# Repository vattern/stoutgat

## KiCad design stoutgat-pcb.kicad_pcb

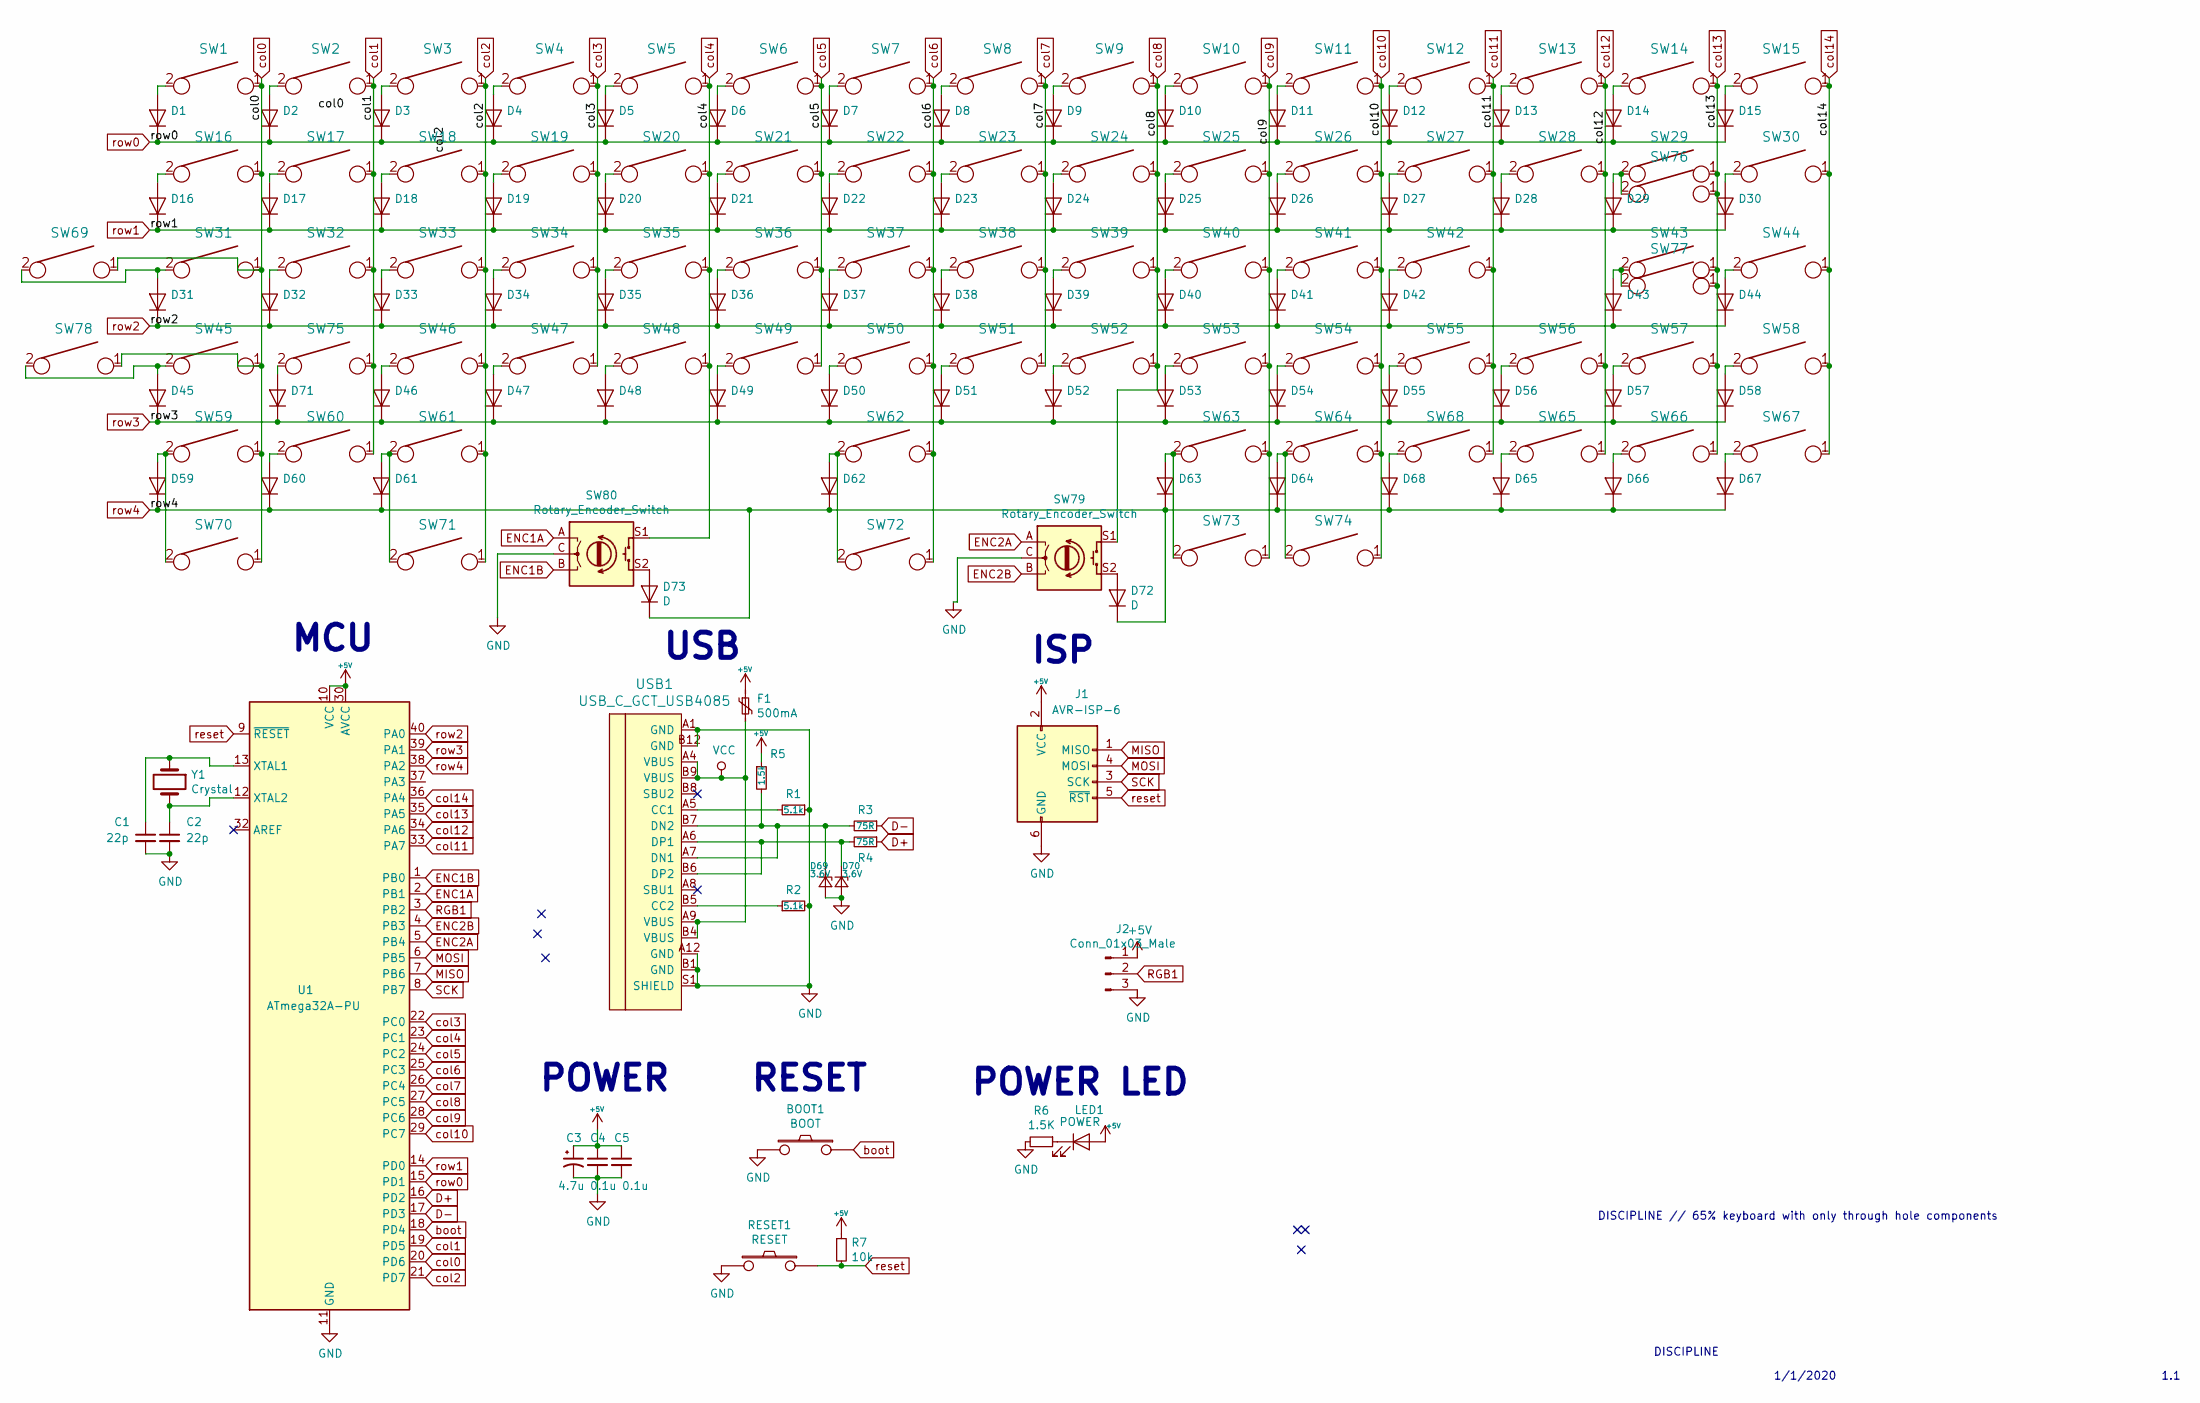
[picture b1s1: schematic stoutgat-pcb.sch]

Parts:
BOOT1: BOOT; SW_PUSH_6mm
C1, C2: 22p; C_Disc_D3.0mm_W1.6mm_P2.50mm
C3: 4.7u; CP_Radial_D4.0mm_P1.50mm
C4, C5: 0.1u; C_Disc_D4.3mm_W1.9mm_P5.00mm
D1, D2, D3, D4, D5, D6, D7, D8, D9, D10, D11, D12, D13, D14, D15, D16, D17, D18, D19, D20, D21, D22, D23, D24, D25, D26, D27, D28, D29, D30, D31, D32, D33, D34, D35, D36, D37, D38, D39, D40, D41, D42, D43, D44, D45, D46, D47, D48, D49, D50, D51, D52, D53, D54, D55, D56, D57, D58, D59, D60, D61, D62, D63, D64, D65, D66, D67, D68, D71: D_DO-35_SOD27_P7.62mm_Horizontal
D69, D70: 3.6V; D_DO-35_SOD27_P7.62mm_Horizontal
D72, D73: D; D_A-405_P7.62mm_Horizontal
F1: 500mA; C_Disc_D5.0mm_W2.5mm_P5.00mm
J1: AVR-ISP-6; PinHeader_2x03_P2.54mm_Vertical
J2: Conn_01x03_Male; PinHeader_1x03_P2.54mm_Vertical
LED1: POWER; LED_D3.0mm
R1, R2: 5.1k; R_Axial_DIN0204_L3.6mm_D1.6mm_P5.08mm_Horizontal
R3, R4: 75R; R_Axial_DIN0204_L3.6mm_D1.6mm_P5.08mm_Horizontal
R5: 1.5k; R_Axial_DIN0204_L3.6mm_D1.6mm_P5.08mm_Horizontal
R6: 1.5K; R_Axial_DIN0204_L3.6mm_D1.6mm_P5.08mm_Horizontal
R7: 10k; R_Axial_DIN0204_L3.6mm_D1.6mm_P5.08mm_Horizontal
RESET1: RESET; SW_PUSH_6mm
SW1, SW2, SW3, SW4, SW5, SW6, SW7, SW8, SW9, SW10, SW11, SW12, SW13, SW15, SW17, SW18, SW19, SW20, SW21, SW22, SW23, SW24, SW25, SW26, SW27, SW28, SW30, SW32, SW33, SW34, SW35, SW36, SW37, SW38, SW39, SW40, SW41, SW42, SW44, SW46, SW47, SW48, SW49, SW50, SW51, SW52, SW53, SW54, SW55, SW57, SW58, SW62, SW65, SW66, SW67, SW68, SW72, SW75, SW77: KEYSW; SW_Cherry_MX_1.00u_PCB
SW14: KEYSW; SW_Cherry_MX_2.00u_PCB
SW16, SW29, SW70, SW71, SW73, SW74: KEYSW; SW_Cherry_MX_1.50u_PCB
SW31, SW56: KEYSW; SW_Cherry_MX_1.75u_PCB
SW43, SW45: KEYSW; SW_Cherry_MX_2.25u_PCB
SW59, SW60, SW61, SW63, SW64, SW69, SW78: KEYSW; SW_Cherry_MX_1.25u_PCB
SW76: KEYSW; SW_Cherry_MX_ISOEnter_PCB
SW79, SW80: Rotary_Encoder_Switch; RotaryEncoder_Alps_EC11E-Switch_Vertical_H20mm
U1: ATmega32A-PU; DIP-40_W15.24mm_Socket
USB1: USB_C_GCT_USB4085; USB_C_Receptacle_GCT_USB4085
Y1: Crystal; Crystal_HC49-4H_Vertical

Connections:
+5V: C3.1, C4.1, C5.1, F1.1, J1.2 (VCC), J2.1, LED1.2 (A), R5.1, R7.1, U1.10 (VCC), U1.30 (AVCC)
D+: R4.1, U1.16 (PD2)
D-: R3.1, U1.17 (PD3)
ENC1A: SW80.A, U1.2 (PB1)
ENC1B: SW80.B, U1.1 (PB0)
ENC2A: SW79.A, U1.5 (PB4)
ENC2B: SW79.B, U1.4 (PB3)
GND: BOOT1.1, C1.2, C2.2, C3.2, C4.2, C5.2, D69.2 (A), D70.2 (A), J1.6 (GND), J2.3, R1.1, R2.2, R6.2, RESET1.1, SW79.C, SW80.C, U1.11 (GND), U1.31 (GND), USB1.A1 (GND), USB1.A12 (GND), USB1.B1 (GND), USB1.B12 (GND), USB1.S1 (SHIELD)
MISO: J1.1 (MISO), U1.7 (PB6)
MOSI: J1.4 (MOSI), U1.6 (PB5)
unnamed: C1.1, U1.13 (XTAL1), Y1.1
unnamed: C2.1, U1.12 (XTAL2), Y1.2
unnamed: D1.2 (A), SW1.2
unnamed: D2.2 (A), SW2.2
unnamed: D3.2 (A), SW3.2
unnamed: D4.2 (A), SW4.2
unnamed: D5.2 (A), SW5.2
unnamed: D6.2 (A), SW6.2
unnamed: D7.2 (A), SW7.2
unnamed: D8.2 (A), SW8.2
unnamed: D9.2 (A), SW9.2
unnamed: D10.2 (A), SW10.2
unnamed: D11.2 (A), SW11.2
unnamed: D12.2 (A), SW12.2
unnamed: D13.2 (A), SW13.2
unnamed: D14.2 (A), SW14.2
unnamed: D15.2 (A), SW15.2
unnamed: D16.2 (A), SW16.2
unnamed: D17.2 (A), SW17.2
unnamed: D18.2 (A), SW18.2
unnamed: D19.2 (A), SW19.2
unnamed: D20.2 (A), SW20.2
unnamed: D21.2 (A), SW21.2
unnamed: D22.2 (A), SW22.2
unnamed: D23.2 (A), SW23.2
unnamed: D24.2 (A), SW24.2
unnamed: D25.2 (A), SW25.2
unnamed: D26.2 (A), SW26.2
unnamed: D27.2 (A), SW27.2
unnamed: D28.2 (A), SW28.2
unnamed: D29.2 (A), SW29.2, SW76.2
unnamed: D30.2 (A), SW30.2
unnamed: D31.2 (A), SW31.2, SW69.2
unnamed: D32.2 (A), SW32.2
unnamed: D33.2 (A), SW33.2
unnamed: D34.2 (A), SW34.2
unnamed: D35.2 (A), SW35.2
unnamed: D36.2 (A), SW36.2
unnamed: D37.2 (A), SW37.2
unnamed: D38.2 (A), SW38.2
unnamed: D39.2 (A), SW39.2
unnamed: D40.2 (A), SW40.2
unnamed: D41.2 (A), SW41.2
unnamed: D42.2 (A), SW42.2
unnamed: D43.2 (A), SW43.2, SW77.2
unnamed: D44.2 (A), SW44.2
unnamed: D45.2 (A), SW45.2, SW78.2
unnamed: D46.2 (A), SW46.2
unnamed: D47.2 (A), SW47.2
unnamed: D48.2 (A), SW48.2
unnamed: D49.2 (A), SW49.2
unnamed: D50.2 (A), SW50.2
unnamed: D51.2 (A), SW51.2
unnamed: D52.2 (A), SW52.2
unnamed: D53.2 (A), SW53.2
unnamed: D54.2 (A), SW54.2
unnamed: D55.2 (A), SW55.2
unnamed: D56.2 (A), SW56.2
unnamed: D57.2 (A), SW57.2
unnamed: D58.2 (A), SW58.2
unnamed: D59.2 (A), SW59.2, SW70.2
unnamed: D60.2 (A), SW60.2
unnamed: D61.2 (A), SW61.2, SW71.2
unnamed: D62.2 (A), SW62.2, SW72.2
unnamed: D63.2 (A), SW63.2, SW73.2
unnamed: D64.2 (A), SW64.2, SW74.2
unnamed: D65.2 (A), SW65.2
unnamed: D66.2 (A), SW66.2
unnamed: D67.2 (A), SW67.2
unnamed: D68.2 (A), SW68.2
unnamed: D69.1 (K), R3.2, R5.2, USB1.A7 (DN1), USB1.B7 (DN2)
unnamed: D70.1 (K), R4.2, USB1.A6 (DP1), USB1.B6 (DP2)
unnamed: D71.2 (A), SW75.2
unnamed: D72.2 (A), SW79.S2
unnamed: D73.2 (A), SW80.S2
unnamed: LED1.1 (K), R6.1
unnamed: R1.2, USB1.A5 (CC1)
unnamed: R2.1, USB1.B5 (CC2)
RGB1: J2.2, U1.3 (PB2)
SCK: J1.3 (SCK), U1.8 (PB7)
VCC: F1.2, USB1.A4 (VBUS), USB1.A9 (VBUS), USB1.B4 (VBUS), USB1.B9 (VBUS)
boot: BOOT1.2, U1.18 (PD4)
col0: SW1.1, SW16.1, SW31.1, SW45.1, SW59.1, SW69.1, SW70.1, SW78.1, U1.20 (PD6)
col1: SW2.1, SW17.1, SW32.1, SW60.1, SW75.1, U1.19 (PD5)
col2: SW3.1, SW18.1, SW33.1, SW46.1, SW61.1, SW71.1, U1.21 (PD7)
col3: SW4.1, SW19.1, SW34.1, SW47.1, U1.22 (PC0)
col4: SW5.1, SW20.1, SW35.1, SW48.1, SW80.S1, U1.23 (PC1)
col5: SW6.1, SW21.1, SW36.1, SW49.1, U1.24 (PC2)
col6: SW7.1, SW22.1, SW37.1, SW50.1, SW62.1, SW72.1, U1.25 (PC3)
col7: SW8.1, SW23.1, SW38.1, SW51.1, U1.26 (PC4)
col8: SW9.1, SW24.1, SW39.1, SW52.1, SW79.S1, U1.27 (PC5)
col9: SW10.1, SW25.1, SW40.1, SW53.1, SW63.1, SW73.1, U1.28 (PC6)
col10: SW11.1, SW26.1, SW41.1, SW54.1, SW64.1, SW74.1, U1.29 (PC7)
col11: SW12.1, SW27.1, SW42.1, SW55.1, SW68.1, U1.33 (PA7)
col12: SW13.1, SW28.1, SW56.1, SW65.1, U1.34 (PA6)
col13: SW14.1, SW29.1, SW43.1, SW57.1, SW66.1, SW76.1, SW77.1, U1.35 (PA5)
col14: SW15.1, SW30.1, SW44.1, SW58.1, SW67.1, U1.36 (PA4)
reset: J1.5 (~RST), R7.2, RESET1.2, U1.9 (~RESET)
row0: D1.1 (K), D2.1 (K), D3.1 (K), D4.1 (K), D5.1 (K), D6.1 (K), D7.1 (K), D8.1 (K), D9.1 (K), D10.1 (K), D11.1 (K), D12.1 (K), D13.1 (K), D14.1 (K), D15.1 (K), U1.15 (PD1)
row1: D16.1 (K), D17.1 (K), D18.1 (K), D19.1 (K), D20.1 (K), D21.1 (K), D22.1 (K), D23.1 (K), D24.1 (K), D25.1 (K), D26.1 (K), D27.1 (K), D28.1 (K), D29.1 (K), D30.1 (K), U1.14 (PD0)
row2: D31.1 (K), D32.1 (K), D33.1 (K), D34.1 (K), D35.1 (K), D36.1 (K), D37.1 (K), D38.1 (K), D39.1 (K), D40.1 (K), D41.1 (K), D42.1 (K), D43.1 (K), D44.1 (K), U1.40 (PA0)
row3: D45.1 (K), D46.1 (K), D47.1 (K), D48.1 (K), D49.1 (K), D50.1 (K), D51.1 (K), D52.1 (K), D53.1 (K), D54.1 (K), D55.1 (K), D56.1 (K), D57.1 (K), D58.1 (K), D71.1 (K), U1.39 (PA1)
row4: D59.1 (K), D60.1 (K), D61.1 (K), D62.1 (K), D63.1 (K), D64.1 (K), D65.1 (K), D66.1 (K), D67.1 (K), D68.1 (K), D72.1 (K), D73.1 (K), U1.38 (PA2)

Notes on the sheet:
DISCIPLINE // 65% keyboard with only through hole components
1/1/2020
DISCIPLINE
1.1
MCU
USB
ISP
POWER
RESET
POWER LED

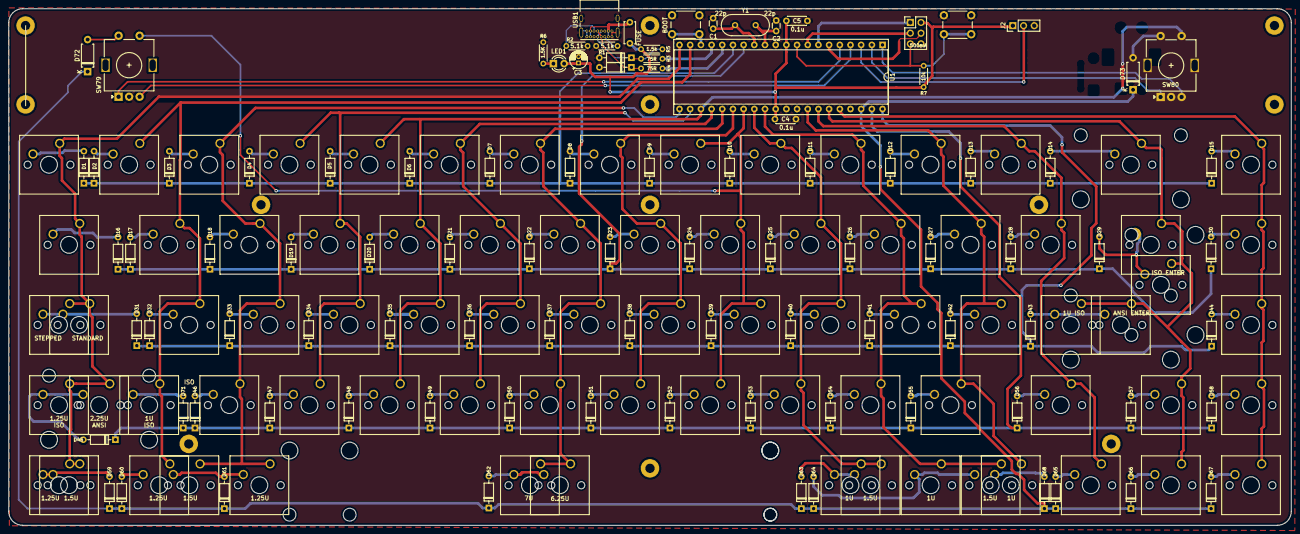
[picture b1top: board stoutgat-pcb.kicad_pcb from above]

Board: 2 copper layers, 304.9 x 122.8 mm, 175 parts (0 on the bottom side), 113 nets.

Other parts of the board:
ST72: 7U; MX-7U-Stabilizer

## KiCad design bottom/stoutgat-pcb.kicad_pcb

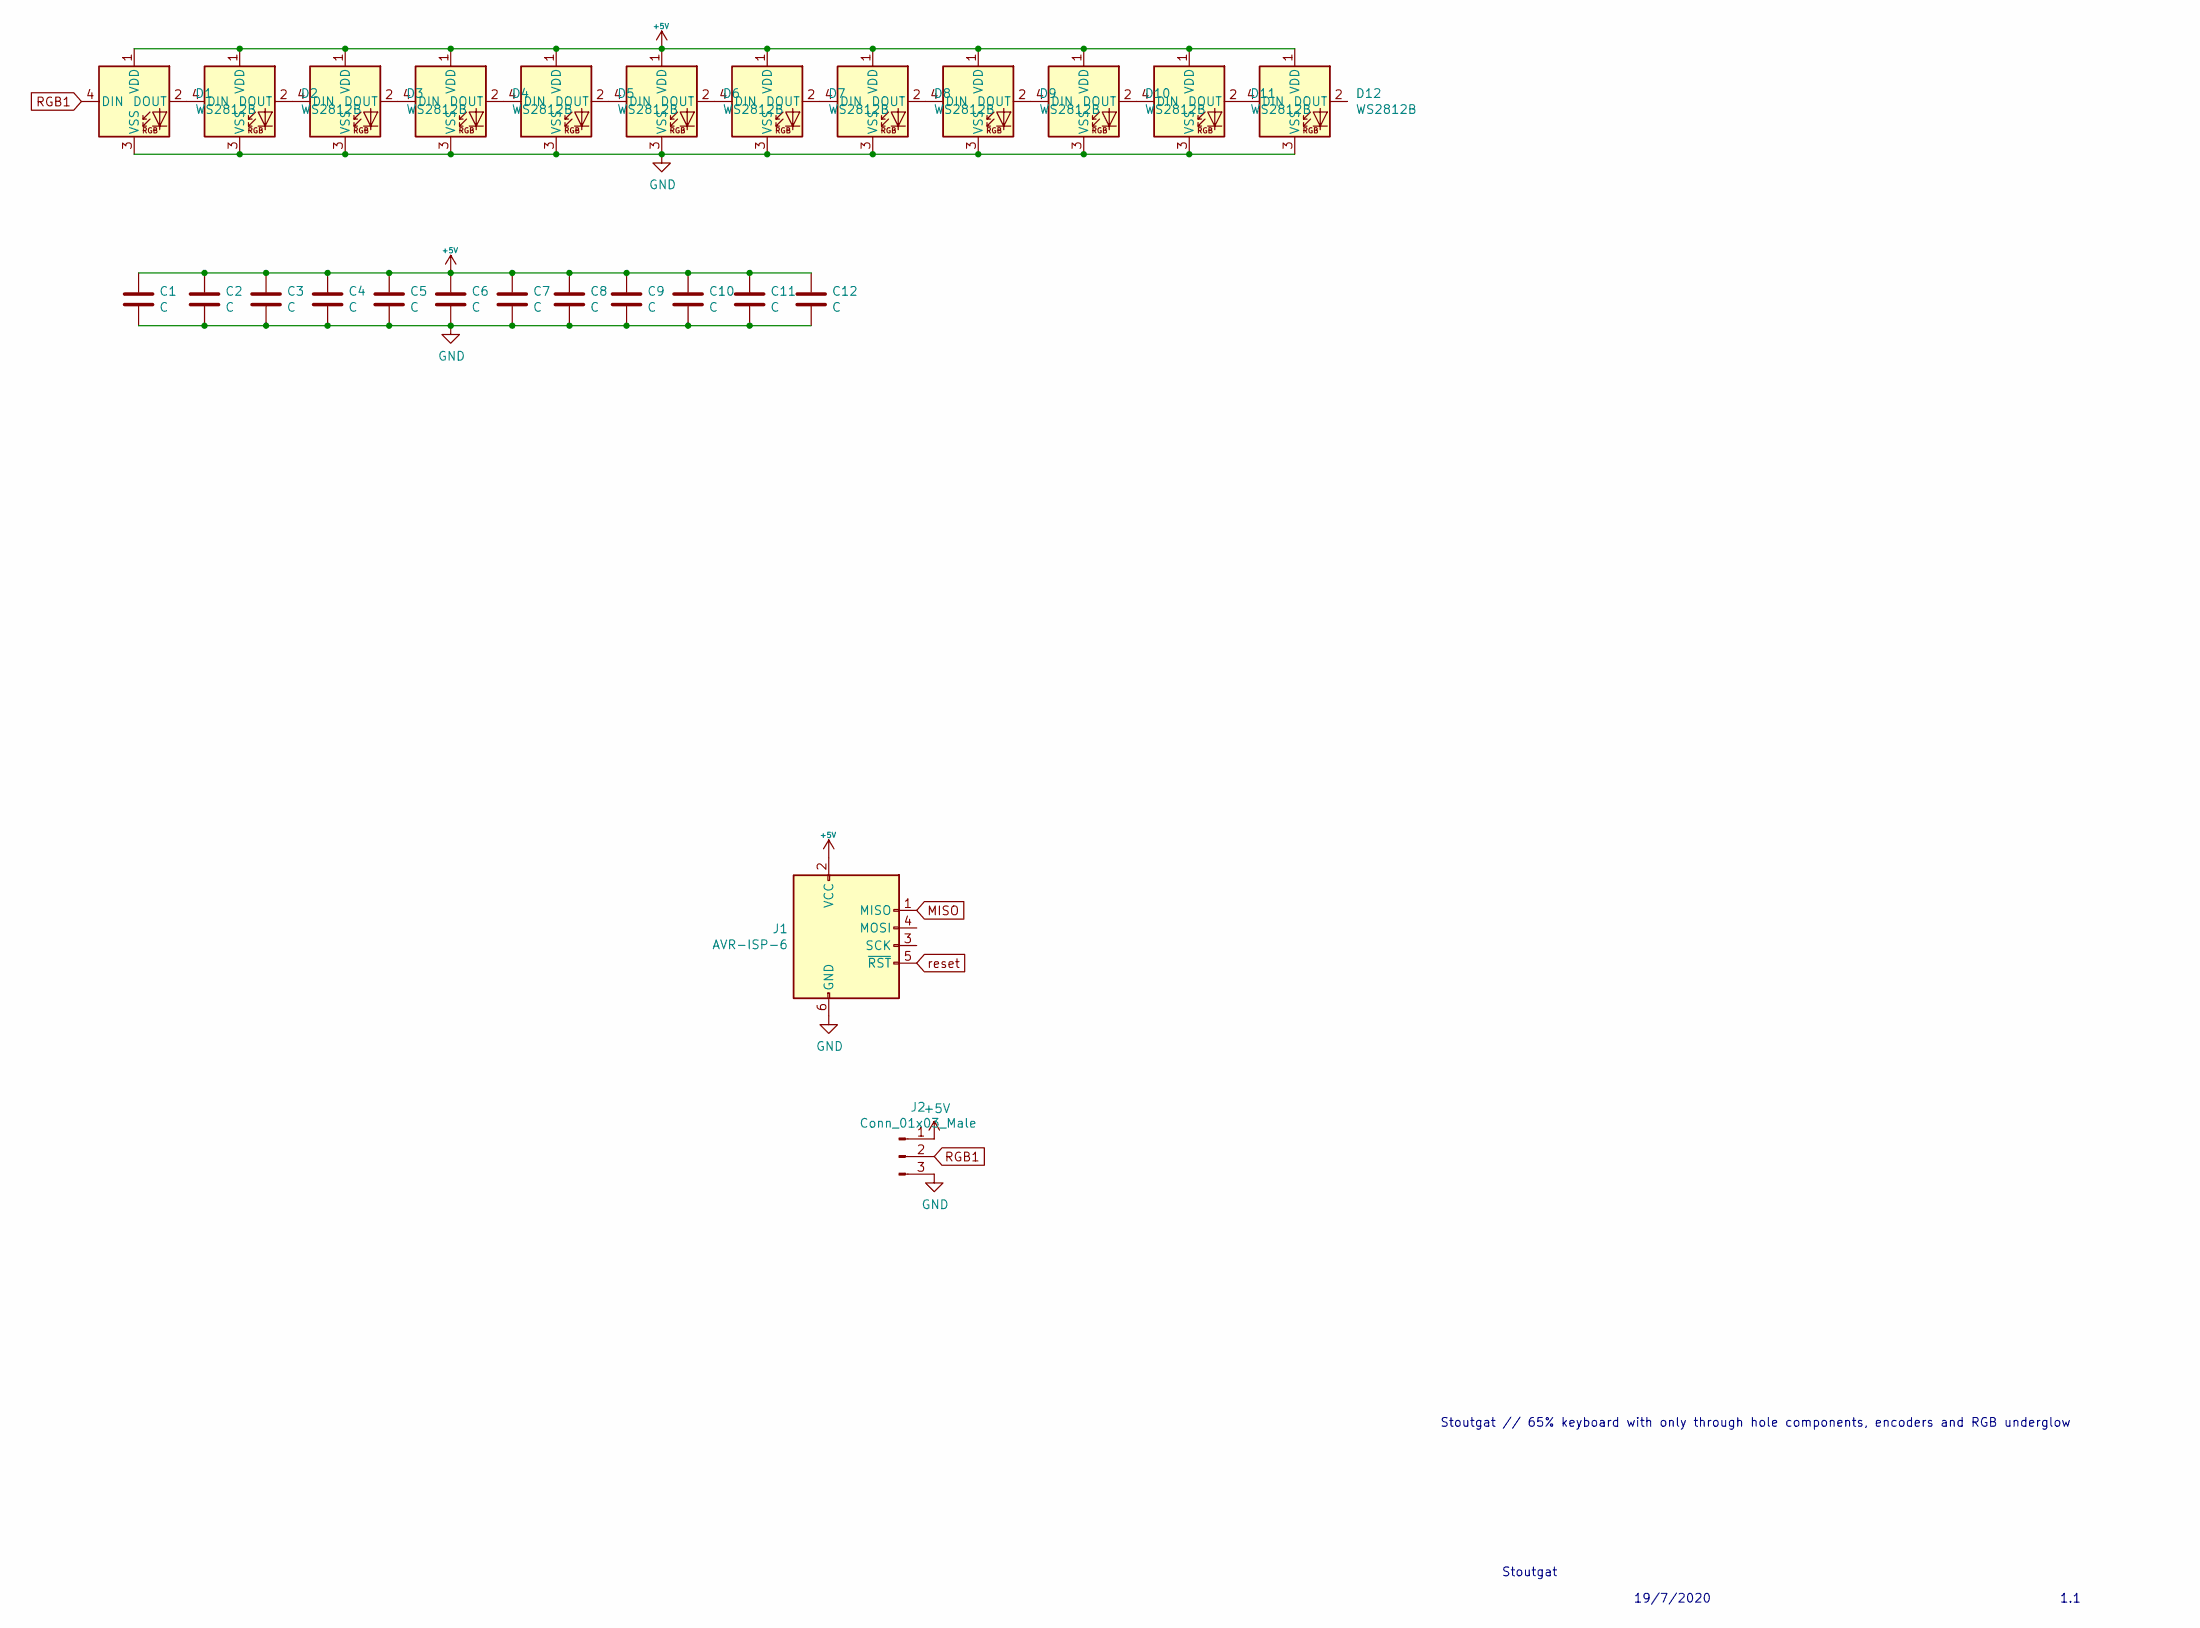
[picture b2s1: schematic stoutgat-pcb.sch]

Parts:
C1, C2, C3, C4, C5, C6, C7, C8, C9, C10, C11, C12: C; C_0805_2012Metric_Pad1.15x1.40mm_HandSolder
D1, D2, D3, D4, D5, D6, D7, D8, D9, D10, D11, D12: WS2812B; LED_WS2812B_PLCC4_5.0x5.0mm_P3.2mm
J1: AVR-ISP-6; PinSocket_2x03_P2.54mm_Vertical
J2: Conn_01x03_Male; PinHeader_1x03_P2.54mm_Vertical

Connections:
+5V: C1.1, C2.1, C3.1, C4.1, C5.1, C6.1, C7.1, C8.1, C9.1, C10.1, C11.1, C12.1, D1.1 (VDD), D2.1 (VDD), D3.1 (VDD), D4.1 (VDD), D5.1 (VDD), D6.1 (VDD), D7.1 (VDD), D8.1 (VDD), D9.1 (VDD), D10.1 (VDD), D11.1 (VDD), D12.1 (VDD), J1.2 (VCC), J2.1
GND: C1.2, C2.2, C3.2, C4.2, C5.2, C6.2, C7.2, C8.2, C9.2, C10.2, C11.2, C12.2, D1.3 (VSS), D2.3 (VSS), D3.3 (VSS), D4.3 (VSS), D5.3 (VSS), D6.3 (VSS), D7.3 (VSS), D8.3 (VSS), D9.3 (VSS), D10.3 (VSS), D11.3 (VSS), D12.3 (VSS), J1.6 (GND), J2.3
MISO: J1.1 (MISO)
unnamed: D1.2 (DOUT), D2.4 (DIN)
unnamed: D2.2 (DOUT), D3.4 (DIN)
unnamed: D3.2 (DOUT), D4.4 (DIN)
unnamed: D4.2 (DOUT), D5.4 (DIN)
unnamed: D5.2 (DOUT), D6.4 (DIN)
unnamed: D6.2 (DOUT), D7.4 (DIN)
unnamed: D7.2 (DOUT), D8.4 (DIN)
unnamed: D8.2 (DOUT), D9.4 (DIN)
unnamed: D10.2 (DOUT), D11.4 (DIN)
unnamed: D9.2 (DOUT), D10.4 (DIN)
unnamed: D11.2 (DOUT), D12.4 (DIN)
RGB1: D1.4 (DIN), J2.2
reset: J1.5 (~RST)

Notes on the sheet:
Stoutgat // 65% keyboard with only through hole components, encoders and RGB underglow
19/7/2020
Stoutgat
1.1

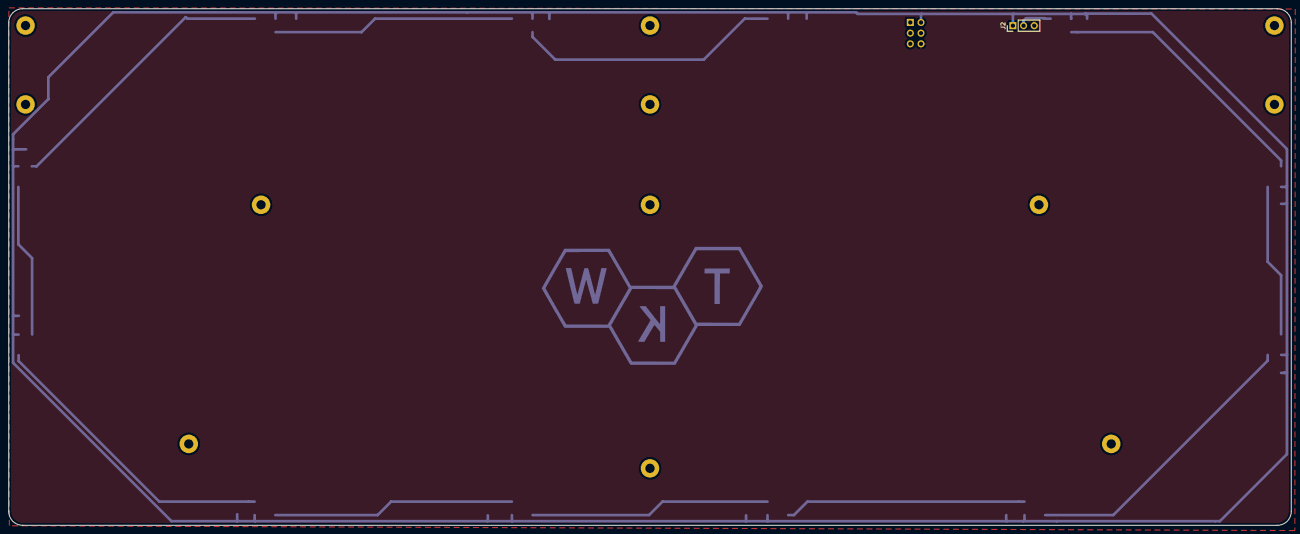
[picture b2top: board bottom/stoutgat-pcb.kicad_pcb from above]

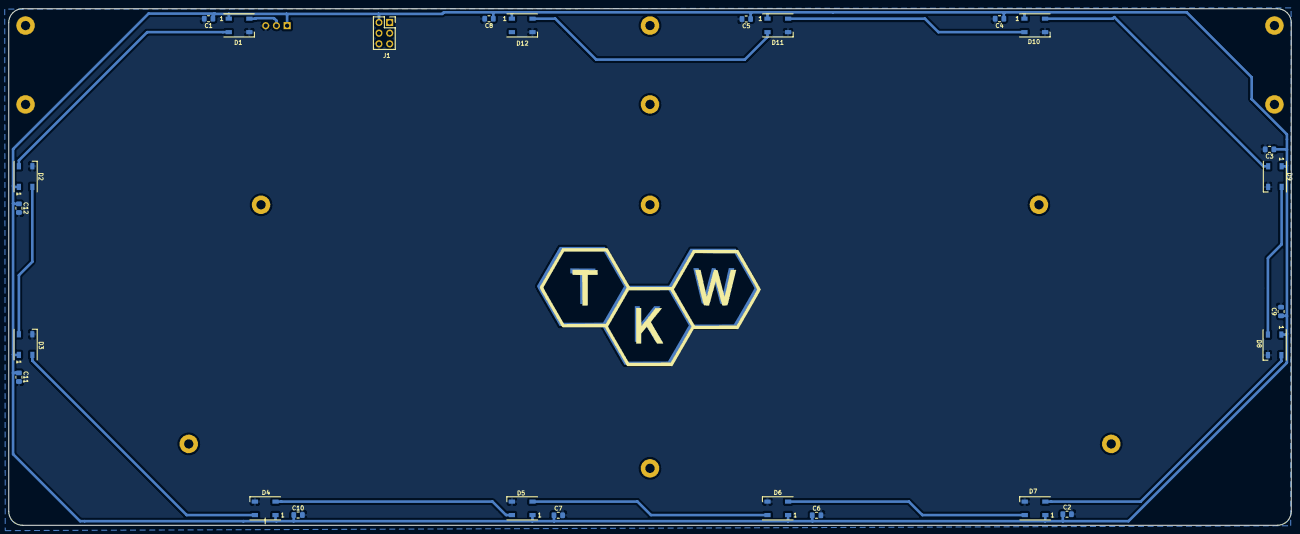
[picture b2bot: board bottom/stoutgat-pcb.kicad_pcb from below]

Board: 2 copper layers, 304.9 x 122.8 mm, 26 parts (25 on the bottom side), 14 nets.

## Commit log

2020-07-26 Initial add
